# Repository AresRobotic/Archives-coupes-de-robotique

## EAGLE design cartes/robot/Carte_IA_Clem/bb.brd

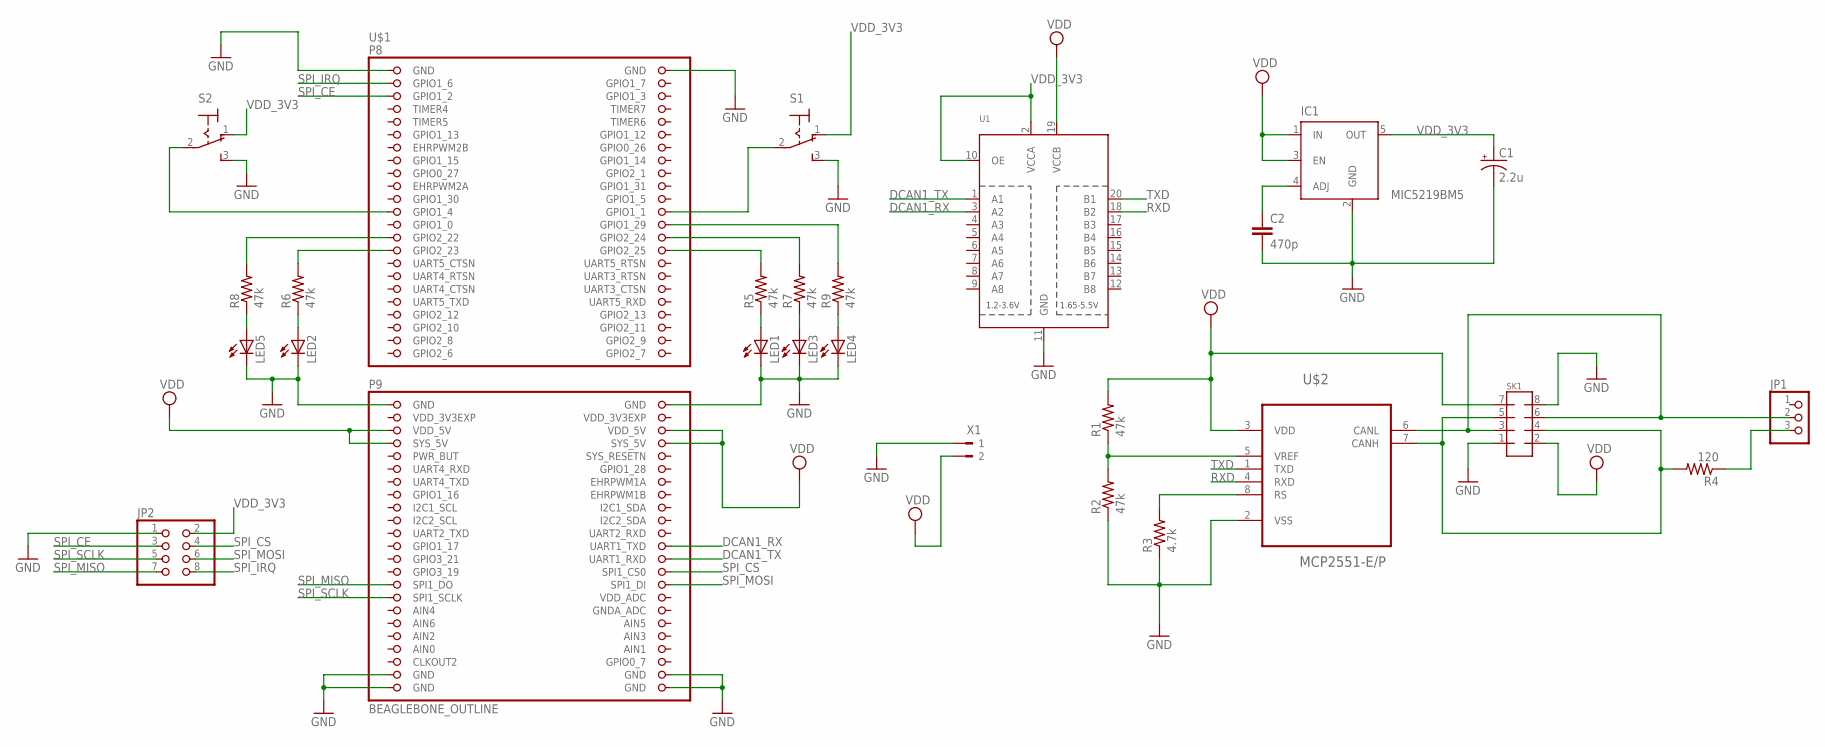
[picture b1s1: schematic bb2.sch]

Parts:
C1: 2.2u; E5-4
C2: 470p; C025-040X050
IC1: MIC5219BM5; SOT23-5
JP1: PINHD-1X3; 1X03
JP2: PINHD-2X4; 2X04
LED1, LED2, LED3, LED4, LED5: LED5MM
R1, R2, R5, R6, R7, R8, R9: 47k; 0207/9
R3: 4.7k; 0207/9
R4: 120; 0207/9
S1, S2: 320-916
SK1: MMATCH-8-PTH; AMP-215079-8
U1: TXB0108PWR; TSSOP20
U$1: BEAGLEBONE_OUTLINE; BEAGLEBONE_SHIELD
U$2: MCP2551-E/P; DIP254P762X432-8
X1: 180G-2

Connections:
AIN0: U$1.85 (AIN0)
DCAN1_RX: U1.3 (A2), U$1.70 (UART1_TXD)
DCAN1_TX: U1.1 (A1), U$1.72 (UART1_RXD)
GND: C1.-, C2.2, IC1.2 (GND), JP2.1, LED1.K (C), LED2.K (C), LED3.K (C), LED4.K (C), LED5.K (C), R2.1, R3.1, S1.3 (S), S2.3 (S), SK1.1, SK1.8, U1.11 (GND), U$1.1 (GND), U$1.2 (GND), U$1.47 (GND), U$1.48 (GND), U$1.89 (GND), U$1.90 (GND), U$1.91 (GND), U$1.92 (GND), U$2.2 (VSS), X1.1
unnamed: R1.1, R2.2, U$2.5 (VREF)
unnamed: JP1.3, R4.1
unnamed: R3.2, U$2.8 (RS)
unnamed: C2.1, IC1.4 (ADJ)
unnamed: R5.2, U$1.30 (GPIO2_25)
unnamed: R6.2, U$1.29 (GPIO2_23)
unnamed: R7.2, U$1.28 (GPIO2_24)
unnamed: R9.2, U$1.26 (GPIO1_29)
unnamed: LED5.A, R8.1
unnamed: S1.2, U$1.24 (GPIO1_1)
unnamed: S2.2, U$1.23 (GPIO1_4)
unnamed: R8.2, U$1.27 (GPIO2_22)
unnamed: JP1.2, SK1.3, SK1.6, U$2.6 (CANL)
unnamed: R4.2, SK1.4, SK1.5, U$2.7 (CANH)
unnamed: LED2.A, R6.1
unnamed: LED1.A, R5.1
unnamed: LED3.A, R7.1
unnamed: LED4.A, R9.1
RXD: U1.18 (B2), U$2.4 (RXD)
SPI_CE: JP2.3, U$1.5 (GPIO1_2)
SPI_CS: JP2.4, U$1.74 (SPI1_CS0)
SPI_IRQ: JP2.8, U$1.3 (GPIO1_6)
SPI_MISO: JP2.7, U$1.75 (SPI1_DO)
SPI_MOSI: JP2.6, U$1.76 (SPI1_DI)
SPI_SCLK: JP2.5, U$1.77 (SPI1_SCLK)
TXD: U1.20 (B1), U$2.1 (TXD)
VDD: IC1.1 (IN), IC1.3 (EN), R1.2, SK1.2, SK1.7, U1.19 (VCCB), U$1.51 (VDD_5V), U$1.52 (VDD_5V), U$1.53 (SYS_5V), U$1.54 (SYS_5V), U$2.3 (VDD), X1.2
VDD_3V3: C1.+, IC1.5 (OUT), JP2.2, S1.1 (O), S2.1 (O), U1.2 (VCCA), U1.10 (OE)
VDD_3V3EXP: U$1.49 (VDD_3V3EXP), U$1.50 (VDD_3V3EXP)

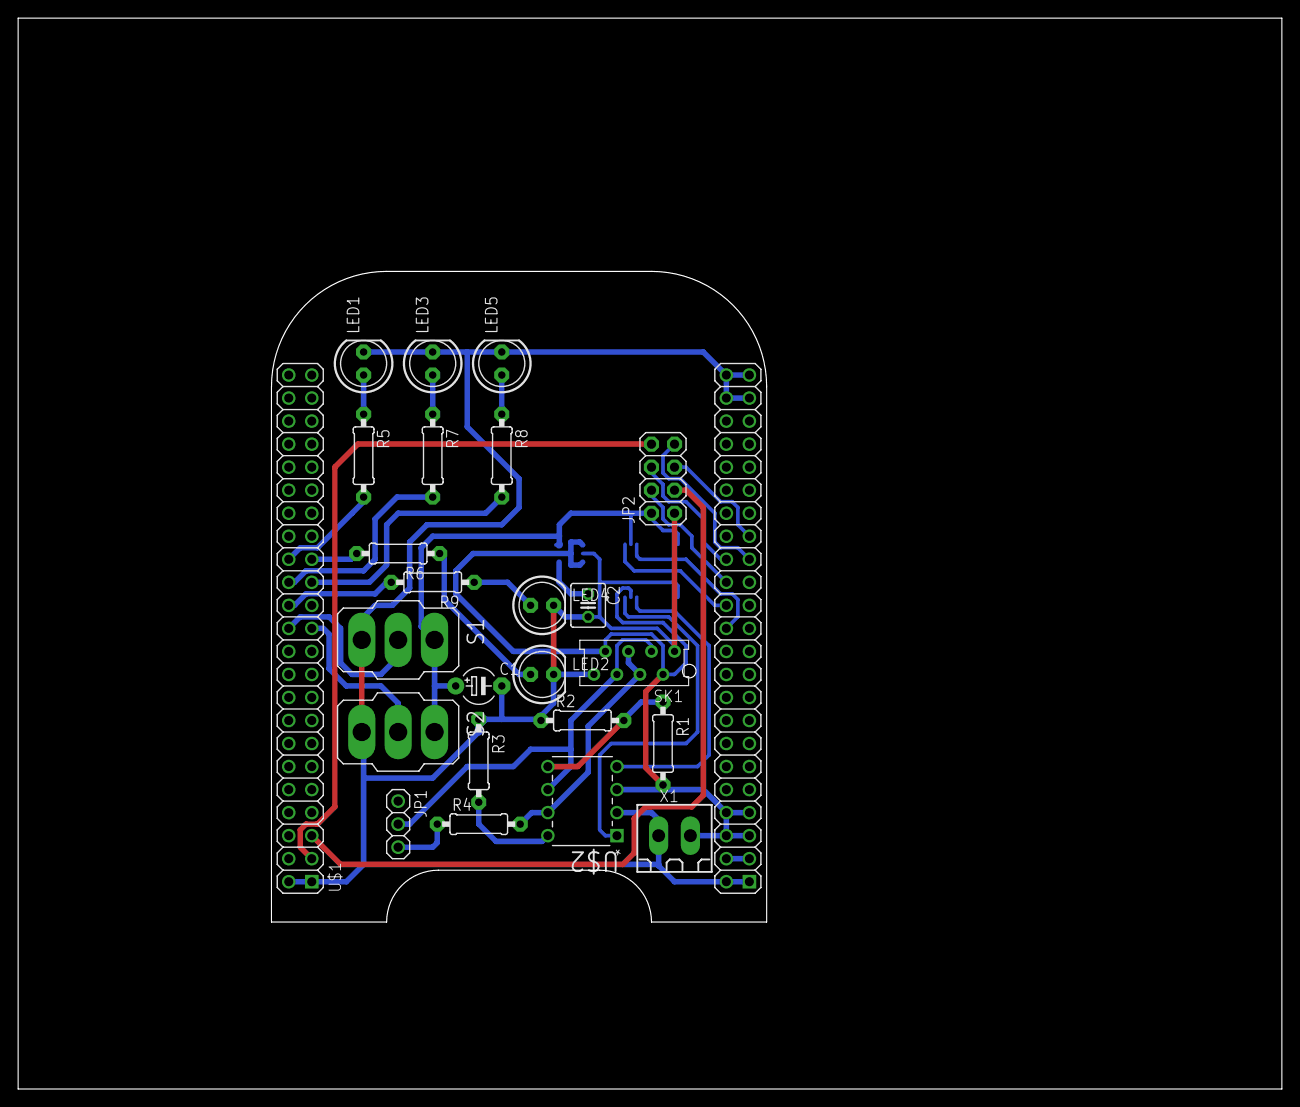
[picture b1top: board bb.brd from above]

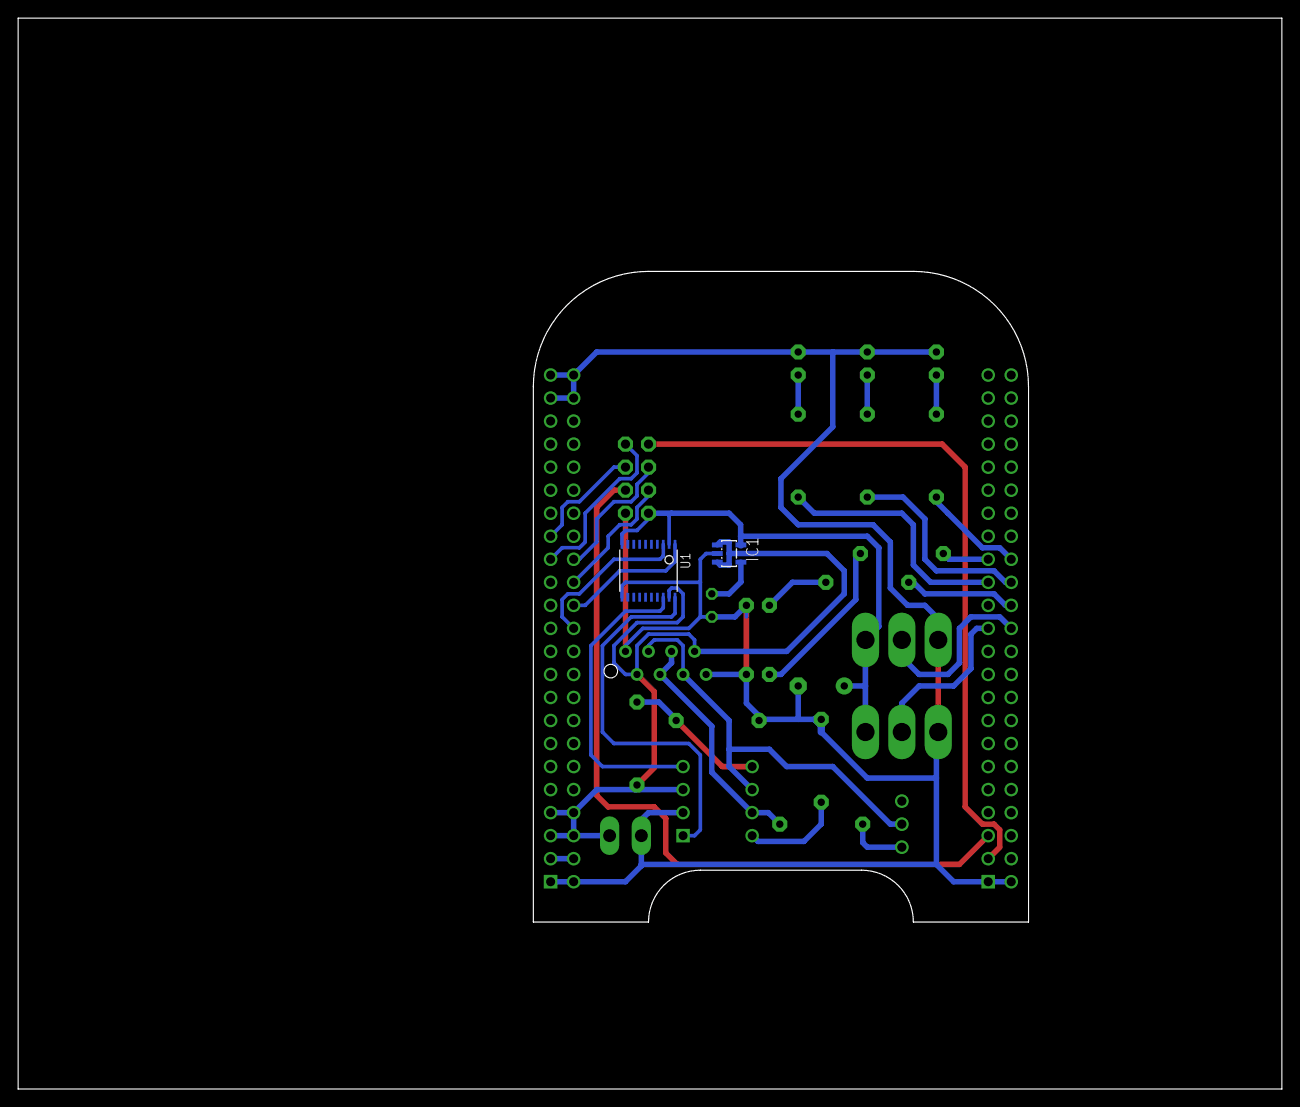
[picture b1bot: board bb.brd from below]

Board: 2 copper layers, 139.4 x 118.1 mm, 26 parts (2 on the bottom side), 32 nets.

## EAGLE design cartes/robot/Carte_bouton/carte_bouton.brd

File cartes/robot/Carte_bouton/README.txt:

* Modifié par Théo le 25/04 à 08:27 pour retourner le connecteur micromatch (au botom) et génrer le GERBER.
* ATTENTION il faut rajouter un switch pour l'alimentation électronique qui sera relié à la carte alim par un molex 2 points par Théo le 26/04 à 14h55

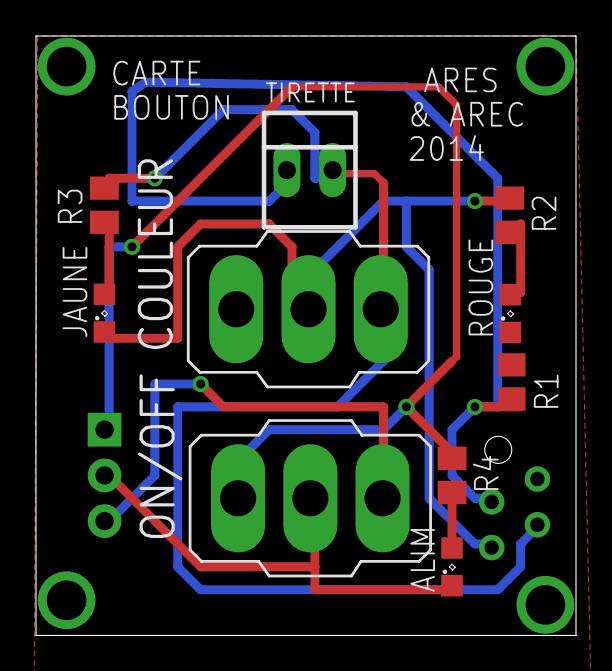
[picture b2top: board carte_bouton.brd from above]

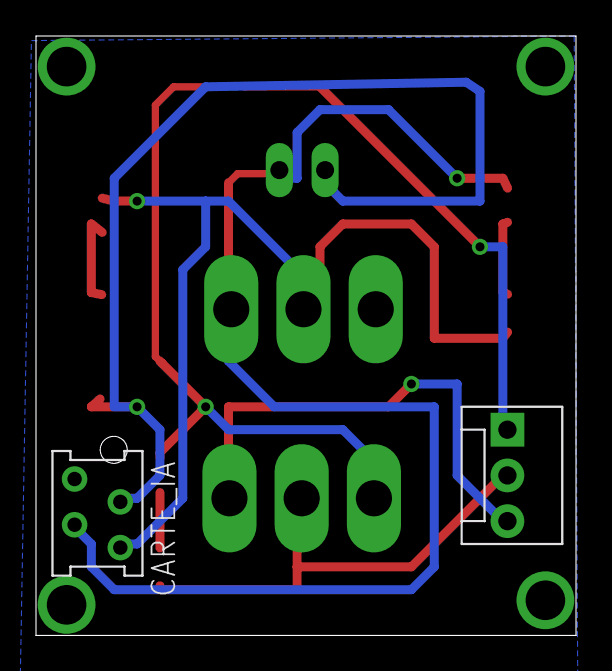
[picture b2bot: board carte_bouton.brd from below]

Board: 2 copper layers, 30.0 x 33.3 mm, 12 parts (2 on the bottom side), 10 nets.

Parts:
ALIM: SML0805
CARTE_ALIM: MOLEX-1X3
CARTE_IA: MMATCH-4-; AMP-215079-4
COULEUR: 320-916
JAUNE: SML0805
ON/OFF: 320-916
R1: R0805
R2, R3, R4: 1k; M0805
ROUGE: SML0805
TIRETTE: 22-23-2021

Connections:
5V: CARTE_ALIM.3, ON/OFF.3
+3V3: CARTE_IA.3, COULEUR.3, R3.2, TIRETTE.2
DATA_SWITCH: ALIM.C, CARTE_ALIM.2, ON/OFF.2
GND: CARTE_IA.1, COULEUR.1, R1.1, ROUGE.C
GND_DIRTY: CARTE_ALIM.1, ON/OFF.1, R4.1
unnamed: CARTE_IA.4, COULEUR.2, JAUNE.C, R2.1
unnamed: R2.2, ROUGE.A
unnamed: JAUNE.A, R3.1
unnamed: ALIM.A, R4.2
TIRETTE: CARTE_IA.2, R1.2, TIRETTE.1

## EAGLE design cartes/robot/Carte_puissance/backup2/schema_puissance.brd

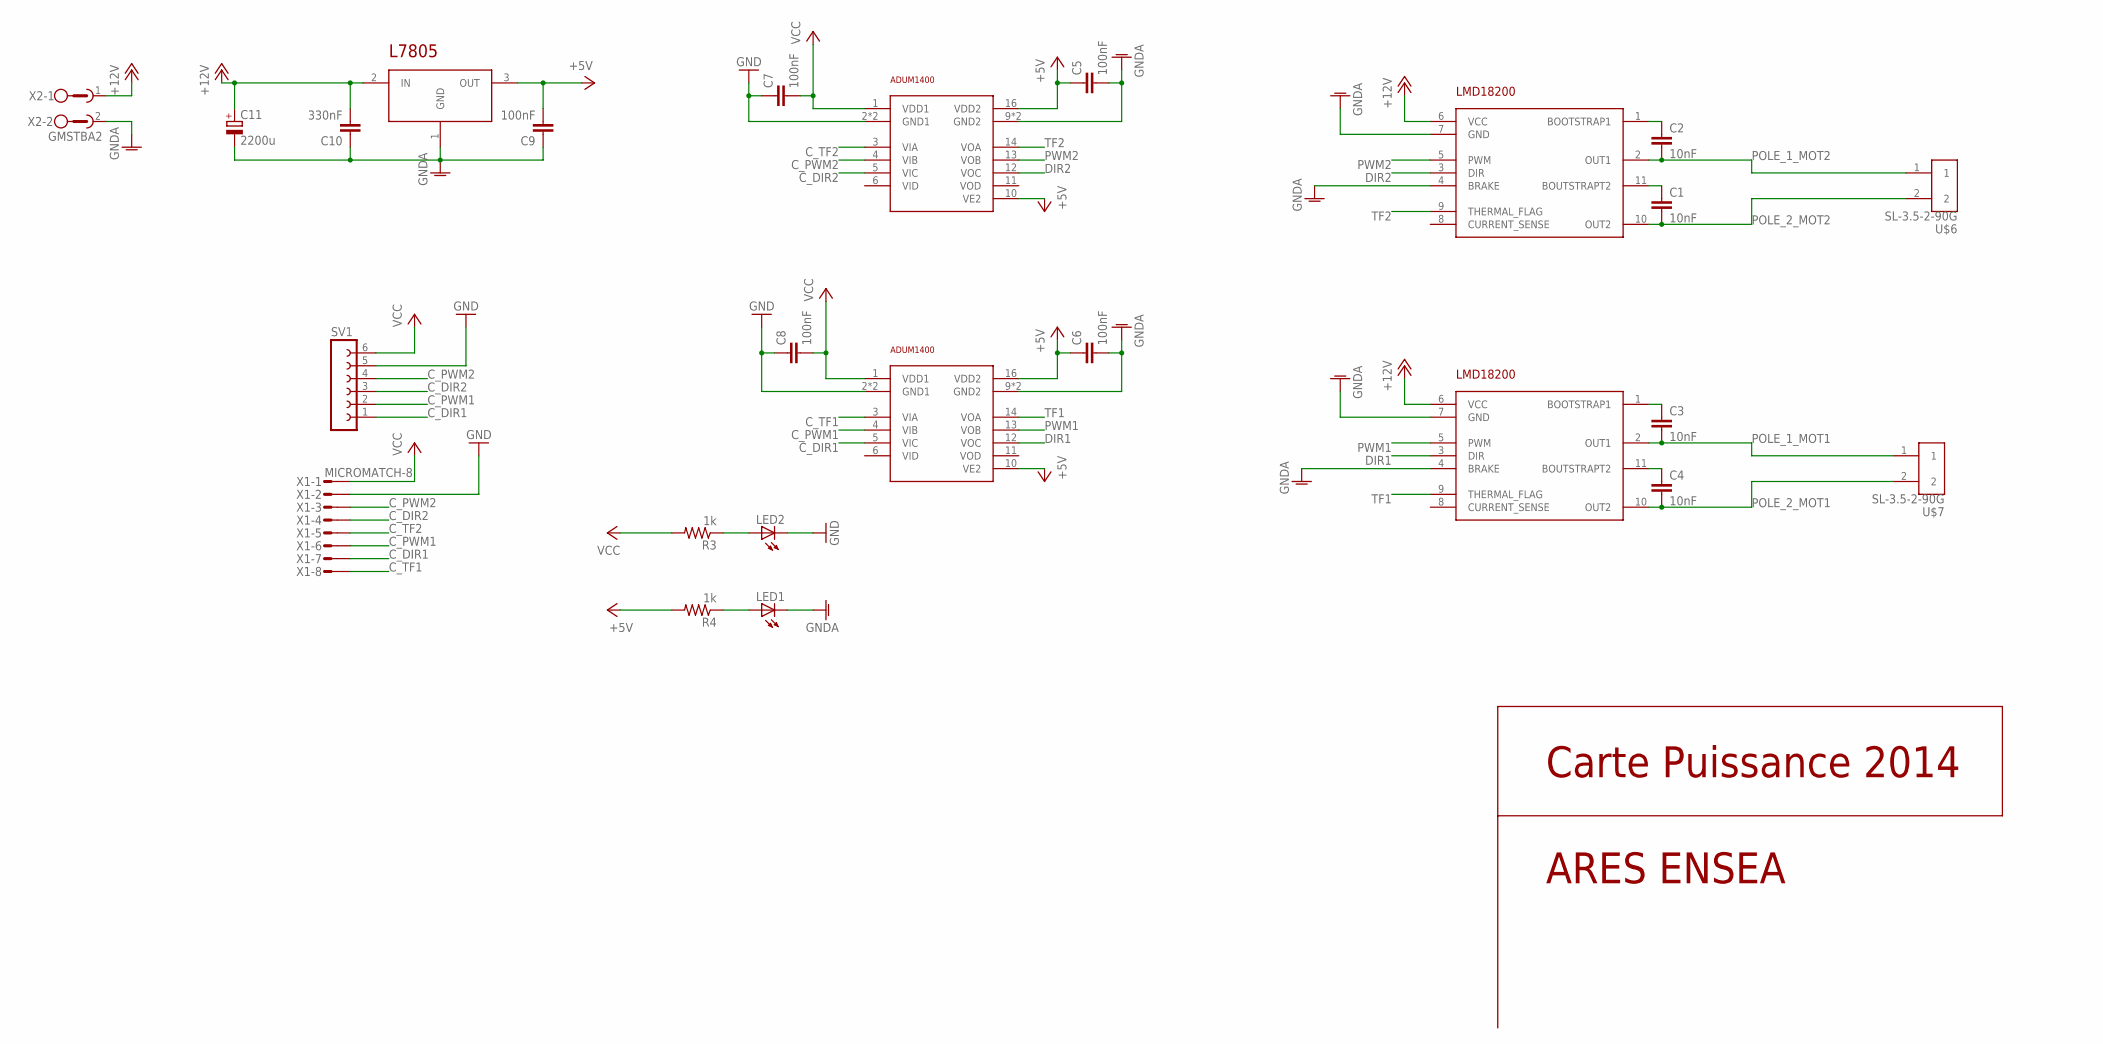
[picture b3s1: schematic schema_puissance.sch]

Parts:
C1, C2, C3, C4: 10nF; C0805
C5, C6, C7, C8, C9: 100nF; C0805
C10: 330nF; C0805
C11: 2200u; TT5D11
LED1, LED2: LEDSML0805; SML0805
R3, R4: 1k; M0805
SV1: FE06-1; FE06
U$1, U$2: LMD18200
U$3, U$4: ADUM1400S; SO-16W
U$5: L7805TO263; DPAK
U$6, U$7: SL-3.5-2-90G
X1: MICROMATCH-8
X2: GMSTBA2

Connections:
+5V: C5.1, C6.1, C9.2, R4.2, U$3.10 (VE2), U$3.16 (VDD2), U$4.10 (VE2), U$4.16 (VDD2), U$5.3 (OUT)
+12V: C10.2, C11.+, U$1.6 (VCC), U$2.6 (VCC), U$5.2 (IN), X2.1
C_DIR1: SV1.1, U$4.5 (VIC), X1.7
C_DIR2: SV1.3, U$3.5 (VIC), X1.4
C_PWM1: SV1.2, U$4.4 (VIB), X1.6
C_PWM2: SV1.4, U$3.4 (VIB), X1.3
C_TF1: U$4.3 (VIA), X1.8
C_TF2: U$3.3 (VIA), X1.5
DIR1: U$1.3 (DIR), U$4.12 (VOC)
DIR2: U$2.3 (DIR), U$3.12 (VOC)
GND: C7.1, C8.1, LED2.C, SV1.5, U$3.2 (GND1), U$3.8 (GND1), U$4.2 (GND1), U$4.8 (GND1), X1.2
GNDA: C5.2, C6.2, C9.1, C10.1, C11.-, LED1.C, U$1.4 (BRAKE), U$1.7 (GND), U$2.4 (BRAKE), U$2.7 (GND), U$3.9 (GND2), U$3.15 (GND2), U$4.9 (GND2), U$4.15 (GND2), U$5.1 (GND), X2.2
unnamed: C1.1, U$2.11 (BOUTSTRAPT2)
unnamed: LED1.A, R4.1
unnamed: C2.1, U$2.1 (BOOTSTRAP1)
unnamed: LED2.A, R3.1
unnamed: C3.1, U$1.1 (BOOTSTRAP1)
unnamed: C4.1, U$1.11 (BOUTSTRAPT2)
POLE_1_MOT1: C3.2, U$1.2 (OUT1), U$7.1
POLE_1_MOT2: C2.2, U$2.2 (OUT1), U$6.1
POLE_2_MOT1: C4.2, U$1.10 (OUT2), U$7.2
POLE_2_MOT2: C1.2, U$2.10 (OUT2), U$6.2
PWM1: U$1.5 (PWM), U$4.13 (VOB)
PWM2: U$2.5 (PWM), U$3.13 (VOB)
TF1: U$1.9 (THERMAL_FLAG), U$4.14 (VOA)
TF2: U$2.9 (THERMAL_FLAG), U$3.14 (VOA)
VCC: C7.2, C8.2, R3.2, SV1.6, U$3.1 (VDD1), U$4.1 (VDD1), X1.1

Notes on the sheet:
Carte Puissance 2014
ARES ENSEA

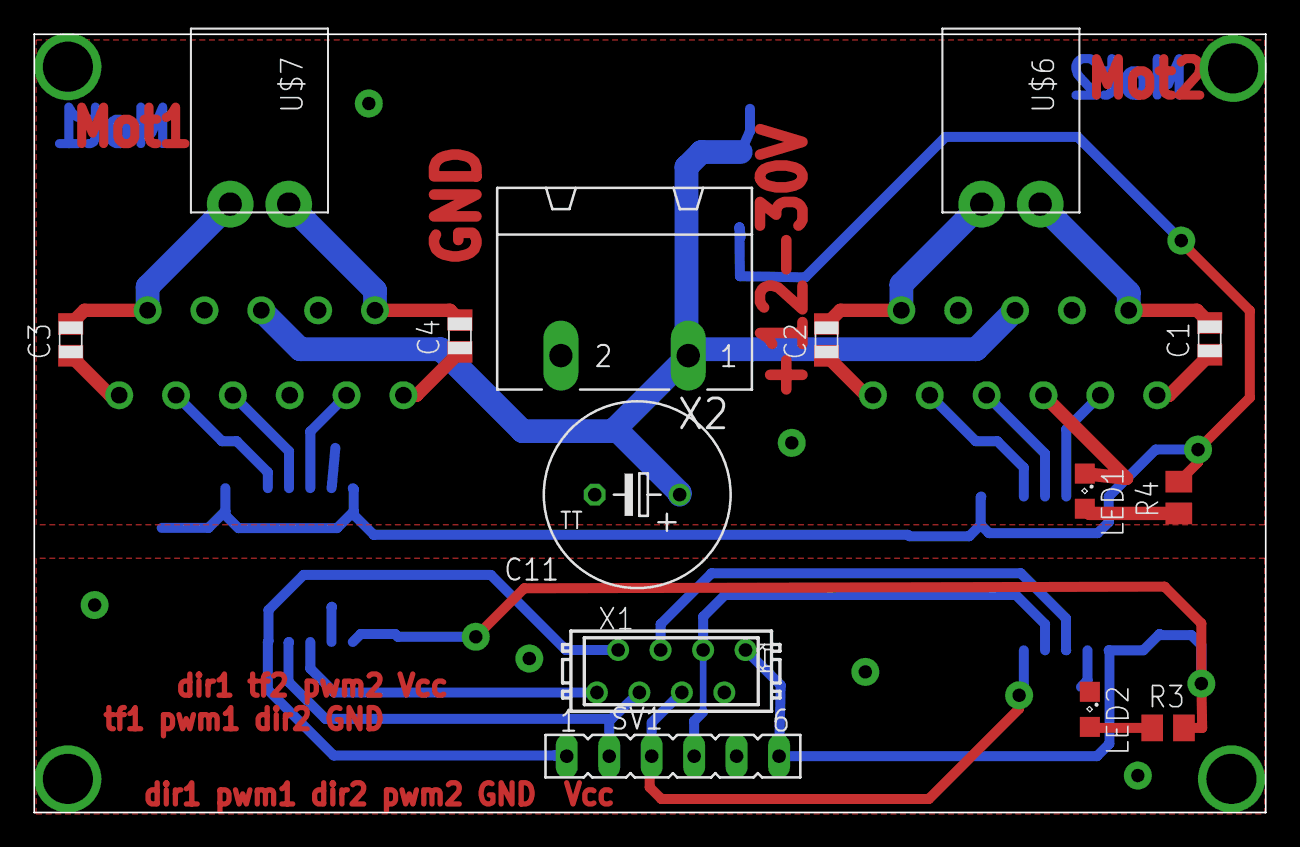
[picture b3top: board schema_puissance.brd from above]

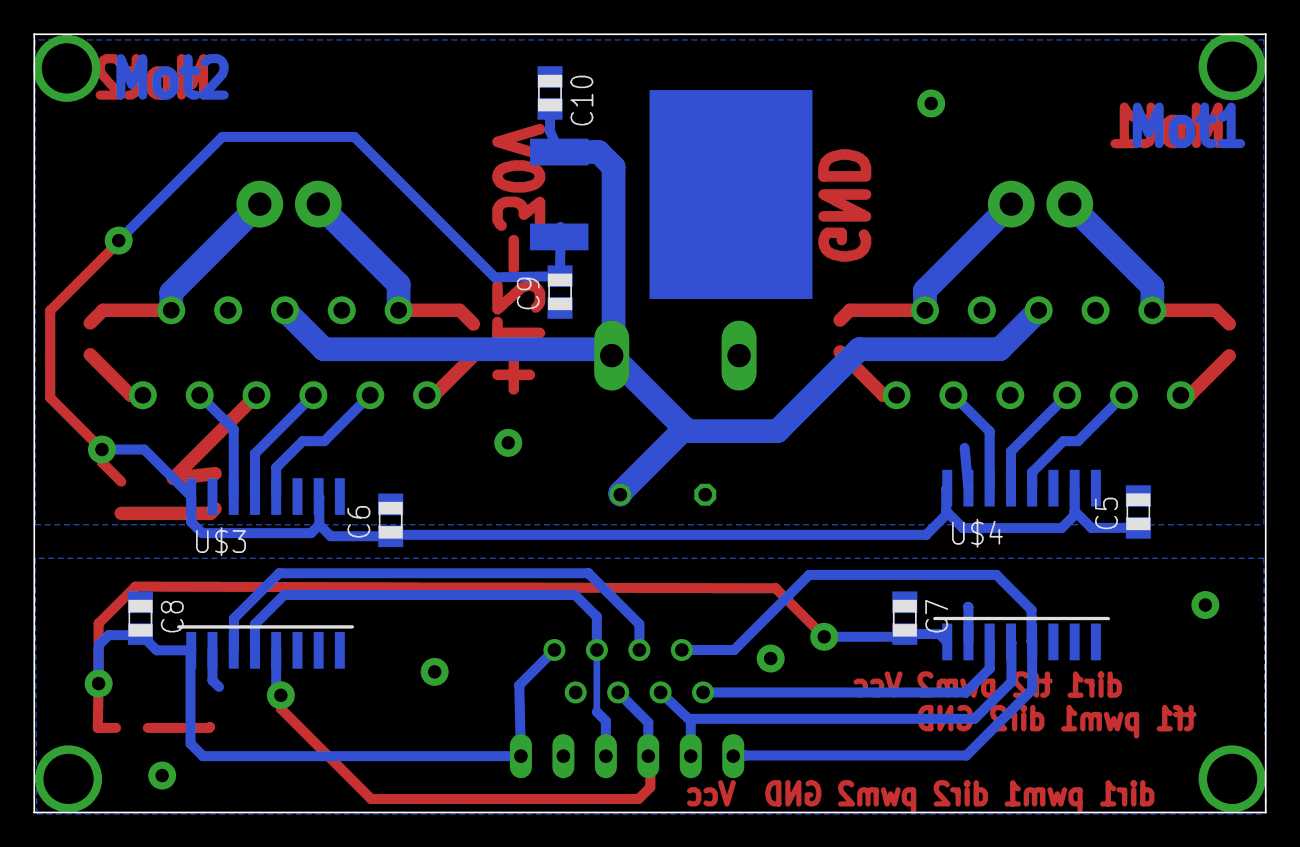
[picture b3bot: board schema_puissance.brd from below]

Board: 2 copper layers, 73.7 x 46.6 mm, 25 parts (9 on the bottom side), 27 nets.

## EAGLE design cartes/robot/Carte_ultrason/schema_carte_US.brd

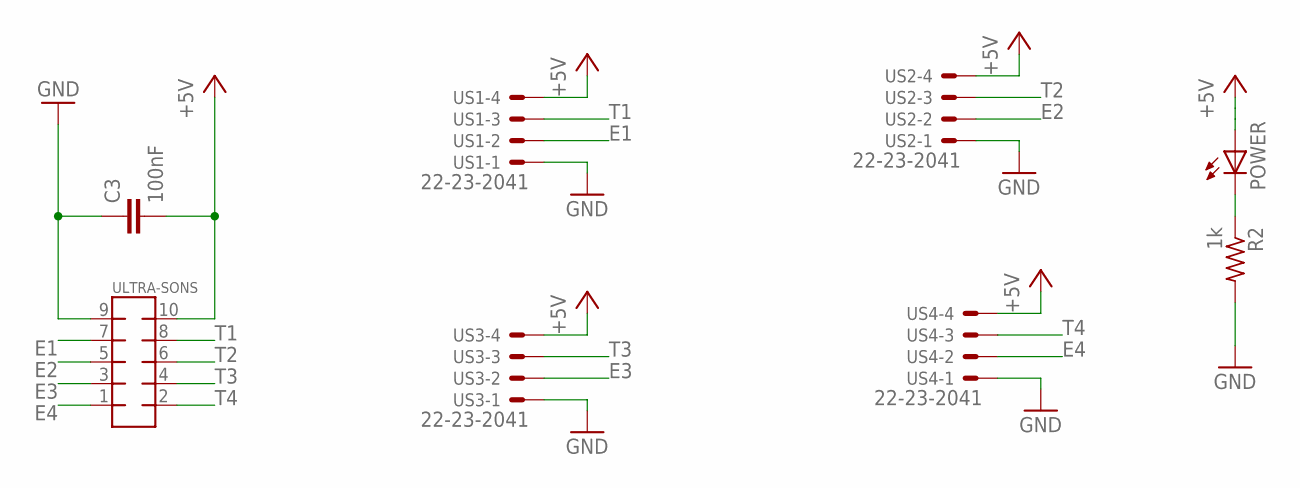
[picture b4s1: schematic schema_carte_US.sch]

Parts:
C3: 100nF; C0805
POWER: LEDCHIPLED_0805; CHIPLED_0805
R2: 1k; M0805
ULTRA-SONS: MMATCH-10-PTH; AMP-215079-10
US1, US2, US3, US4: 22-23-2041

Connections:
+5V: C3.2, POWER.A, ULTRA-SONS.10, US1.4, US2.4, US3.4, US4.4
E1: ULTRA-SONS.7, US1.2
E2: ULTRA-SONS.5, US2.2
E3: ULTRA-SONS.3, US3.2
E4: ULTRA-SONS.1, US4.2
GND: C3.1, R2.2, ULTRA-SONS.9, US1.1, US2.1, US3.1, US4.1
unnamed: POWER.C, R2.1
T1: ULTRA-SONS.8, US1.3
T2: ULTRA-SONS.6, US2.3
T3: ULTRA-SONS.4, US3.3
T4: ULTRA-SONS.2, US4.3

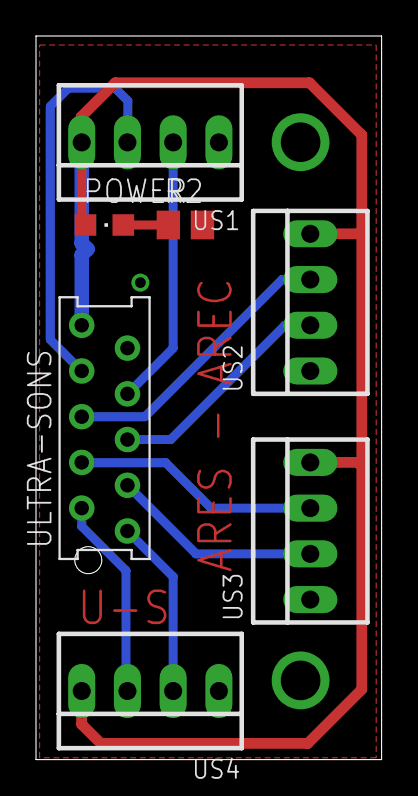
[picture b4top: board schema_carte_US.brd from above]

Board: 2 copper layers, 19.2 x 40.2 mm, 8 parts (1 on the bottom side), 11 nets.

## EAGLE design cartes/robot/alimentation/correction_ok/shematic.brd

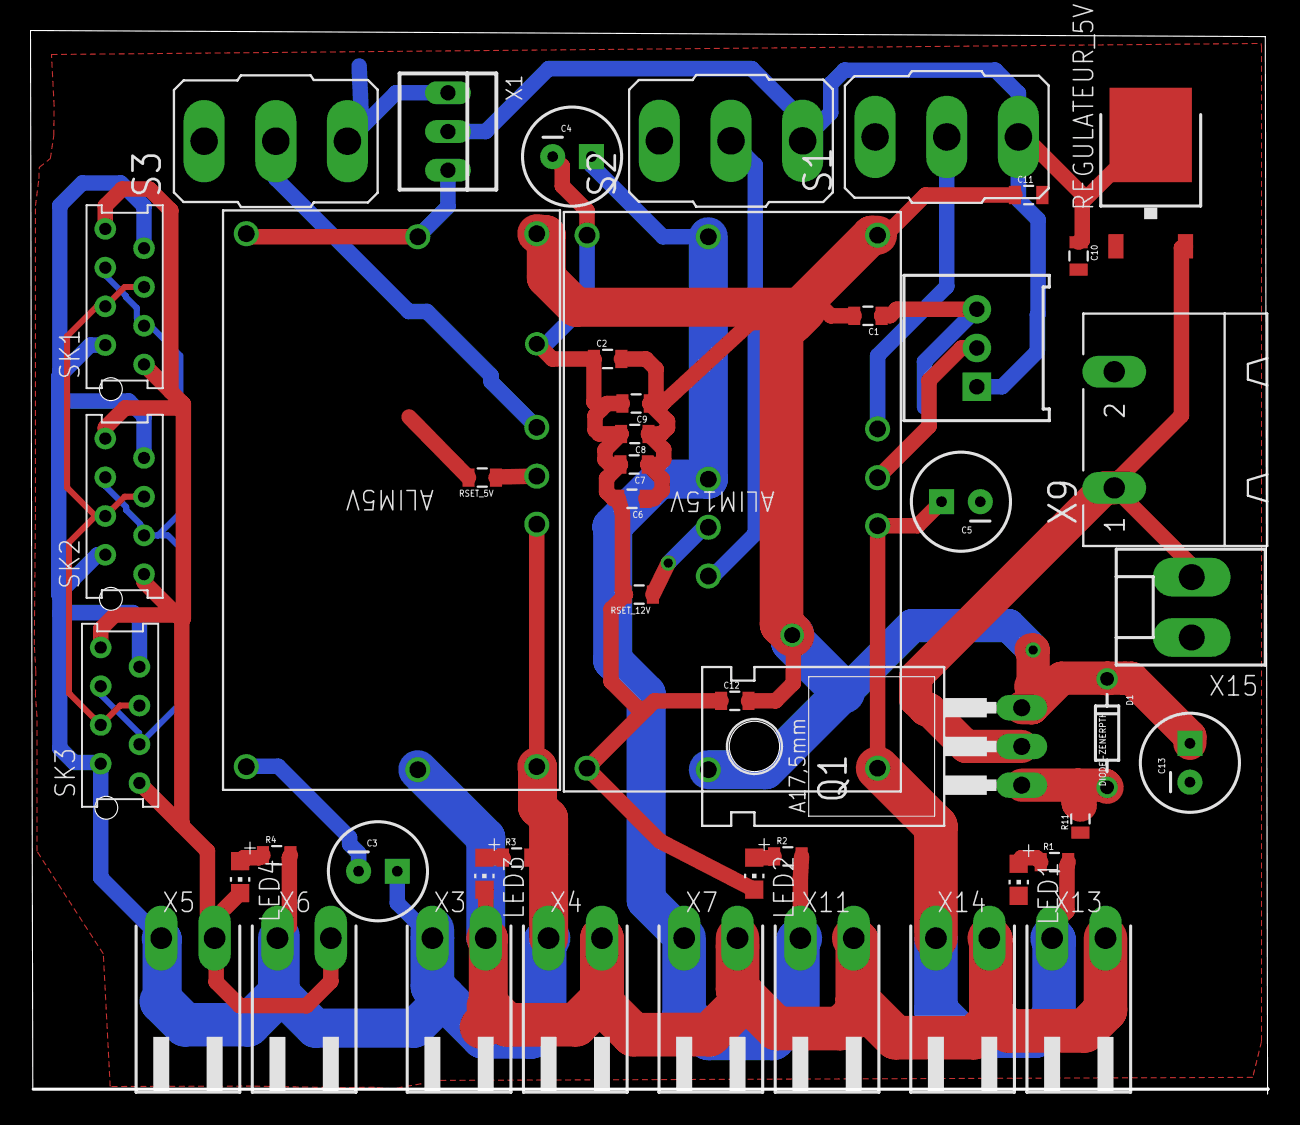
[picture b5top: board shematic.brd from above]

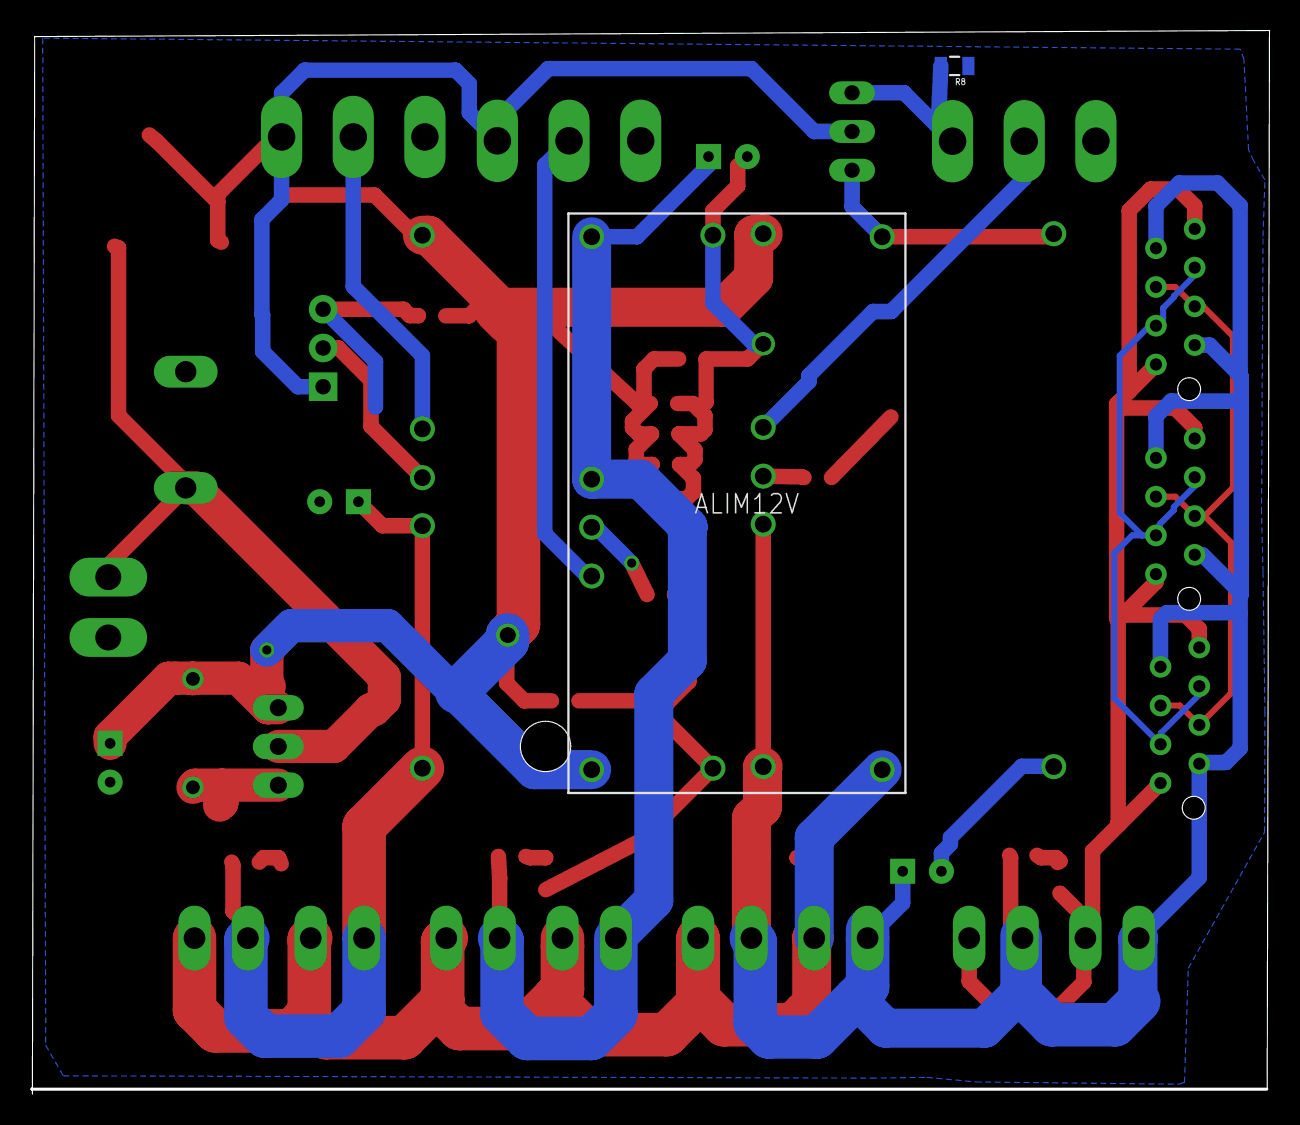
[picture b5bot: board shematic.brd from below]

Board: 2 copper layers, 81.1 x 69.8 mm, 49 parts (2 on the bottom side), 22 nets.

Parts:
ALIM5V, ALIM12V: PTN78020WAH; EUK7
ALIM15V: PTN78020HAH; EUK7
C1, C2, C12: 2.2uF; 0805
C3, C4, C5: 330uF; CPOL-RADIAL-100UF-25V
C6, C7, C8, C9: 4.7uF; 0805
C10: 0.1uF; 0805
C11: 0.33uF; 0805
C13: CPOL-RADIAL-100UF-25V
D1: DIODE-ZENERPTH; DIODE-ZENER
LED1, LED2, LED3, LED4: CHIP-LED0805
MAX=100K: Rset_15v; 3386U
Q1: TO220BH
R1, R2: 2k; 0805
R3, R4: 820; 0805
R8: 1k; 0805
R11: 100k; 0805
REGULATEUR_5V: MC33269D-5.0; DPACK
RSET_5V: 21k; 0805
RSET_12V: 734; 0805
S1, S2, S3: M9040P
SK1, SK2, SK3: AMP-215079-8
X1: 22-23-2031
X3: OUT1_5v; 90-2
X4: OUT2_5v; 90-2
X5: OUT1_T5V; 90-2
X6: OUT2_T5v; 90-2
X7: OUT1_12v; 90-2
X9: IN_batteries; GMSTBA2
X11: OUT2_12v; 90-2
X13: OUT2_15v; 90-2
X14: OUT1_15v; 90-2
X15: prise_Voltmetre; KK-156-2

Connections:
ADJUST_5V: ALIM5V.4, RSET_5V.1
ADJUST_12V: ALIM12V.4, RSET_12V.1
ADJUST_15V: ALIM15V.4, MAX=100K.2
BAT: Q1.D, REGULATEUR_5V.3, X9.1, X15.2
CANH: SK1.4, SK1.5, SK2.4, SK2.5, SK3.4, SK3.5
CANL: SK1.3, SK1.6, SK2.3, SK2.6, SK3.3, SK3.6
GND: ALIM5V.1, ALIM5V.7, ALIM12V.1, ALIM12V.7, ALIM15V.1, ALIM15V.7, C1.1, C2.1, C3.2, C4.2, C5.2, C6.2, C7.2, C8.2, C9.2, C10.2, C11.2, C12.1, C13.2, LED1.C, LED2.C, LED3.C, MAX=100K.3, R8.1, R11.1, REGULATEUR_5V.1, RSET_5V.2, RSET_12V.2, S1.1, S2.1, S3.1, X1.3, X3.2, X4.2, X7.2, X9.2, X11.2, X13.2, X14.2, X15.1
GND_T: LED4.C, SK1.1, SK1.8, SK2.1, SK2.8, SK3.1, SK3.8, X5.2, X6.2
GRILLE: D1.P$2, Q1.G, R11.2
unnamed: LED1.A, R1.1
unnamed: LED2.A, R2.1
unnamed: LED3.A, R3.1
unnamed: LED4.A, R4.1
OUT_5V: ALIM5V.5, ALIM5V.6, C3.1, R3.2, R4.2, SK1.2, SK1.7, SK2.2, SK2.7, SK3.2, SK3.7, X3.1, X4.1, X5.1, X6.1
OUT_12V: ALIM12V.5, ALIM12V.6, C4.1, R2.2, X7.1, X11.1
OUT_15V: ALIM15V.5, ALIM15V.6, C5.1, R1.2, X13.1, X14.1
OUT_INTERR_1: ALIM15V.3, S1.2
OUT_INTERR_2: ALIM12V.3, S2.2
OUT_INTERR_3: ALIM5V.3, S3.2
OUT_MASTER_INTERR: R8.2, S3.3, X1.1
OUT_REG: C10.1, MAX=100K.1, REGULATEUR_5V.2, S1.3, S2.3, X1.2
VBAT: ALIM5V.2, ALIM12V.2, ALIM15V.2, C1.2, C2.2, C6.1, C7.1, C8.1, C9.1, C11.1, C12.2, C13.1, D1.P$1, Q1.S

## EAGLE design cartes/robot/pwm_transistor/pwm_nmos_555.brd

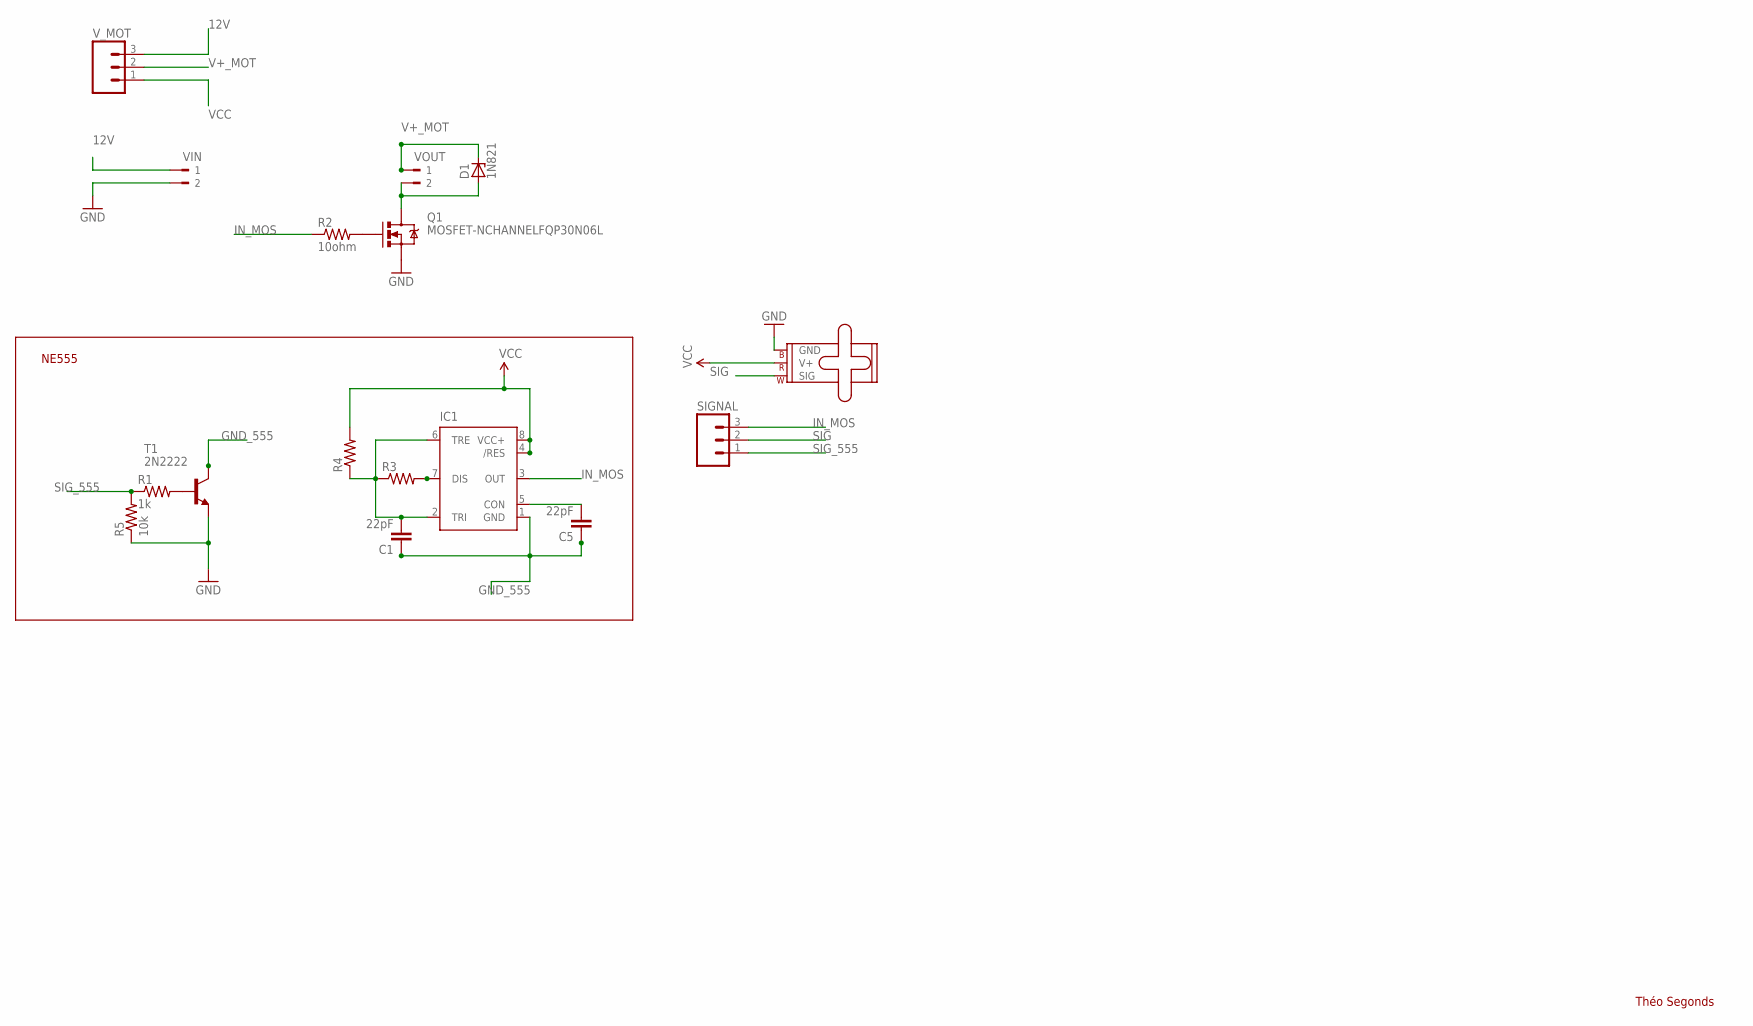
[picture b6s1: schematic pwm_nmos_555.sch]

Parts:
C1, C5: 22pF; 0805; MPN 08055A220JAT2A
D1: 1N821; DO35Z10
IC1: NE555P; DIL-08
INPUT: SMALL_SERVO; 1X03
Q1: MOSFET-NCHANNELFQP30N06L; TO220V
R1: 1k; 0805
R2: 10ohm; 0805
R3, R4: RESISTOR0805-RES; 0805
R5: 10k; 0805
SIGNAL: M03PTH; 1X03
T1: 2N2222; TO92-EBC-OVAL
VIN: 90-2
VOUT: 90-2
V_MOT: M03PTH; 1X03

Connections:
12V: VIN.1, V_MOT.3
GND: INPUT.3 (GND), Q1.3 (S), R5.1, T1.E, VIN.2
GND_555: C1.1, C5.1, IC1.1 (GND), T1.C
IN_MOS: IC1.3 (OUT), R2.1, SIGNAL.3
unnamed: R1.2, T1.B
unnamed: Q1.1 (G), R2.2
unnamed: C1.2, IC1.2 (TRI), IC1.6 (TRE), R3.1, R4.1
unnamed: IC1.7 (DIS), R3.2
unnamed: C5.2, IC1.5 (CON)
SIG: INPUT.1 (SIG), SIGNAL.2
SIG_555: R1.1, R5.2, SIGNAL.1
V+_MOT: D1.C, VOUT.1, V_MOT.2
VCC: IC1.4 (/RES), IC1.8 (VCC+), INPUT.2 (V+), R4.2, V_MOT.1
VOUT: D1.A, Q1.2 (D), VOUT.2

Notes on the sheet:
Théo Segonds
NE555

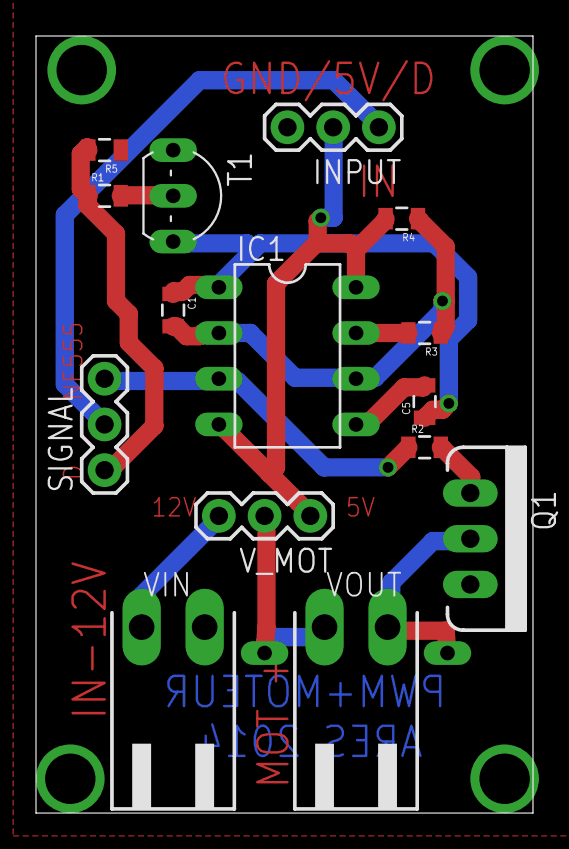
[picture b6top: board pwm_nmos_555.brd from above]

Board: 2 copper layers, 27.6 x 43.2 mm, 16 parts (1 on the bottom side), 14 nets.

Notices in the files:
parts and their libraries:
SparkFun-Connectors: Licensing: CC v3.0 Share-Alike You are welcome to use this library for commercial purposes.
